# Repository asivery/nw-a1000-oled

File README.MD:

# A replacement display for the NW-A1000 Network Walkman

## How it works

Since the Sony NW-A1000 uses an obsolete SSD1328U1-based screen, to make it work with a generic SSD1327 screen I had to patch the firmware.

There's, of course, no new screens available with that exact pinout, so I designed a flex PCB which simply translates the pin layout to the one used by new OLEDs.

[Here](https://aliexpress.com/item/1005006480988390.html)'s the screen I used.

## How to patch?

1. Download the official Sony upgrade tool for the NW-A1000, and start it with the walkman unplugged.
2. Once you see this window, open task manager.

3. Open task manager, find `FWUpdater.exe`, right click, select `Open file location`. Then copy all the files to somewhere on your desktop.

4. Go to [my patching site](https://asivery.github.io/NW-A1000/), and provide it the `ver3.00/NW_A1000.UPG` file from that folder.
5. Download the new file, delete all files in `ver3.00` and replace them with the one from my site.
6. Run the patcher and flash the Walkman.

## Is the NW-A1200 / NW-A3000 supported?

I don't know - I haven't tested them with this method, but probably.

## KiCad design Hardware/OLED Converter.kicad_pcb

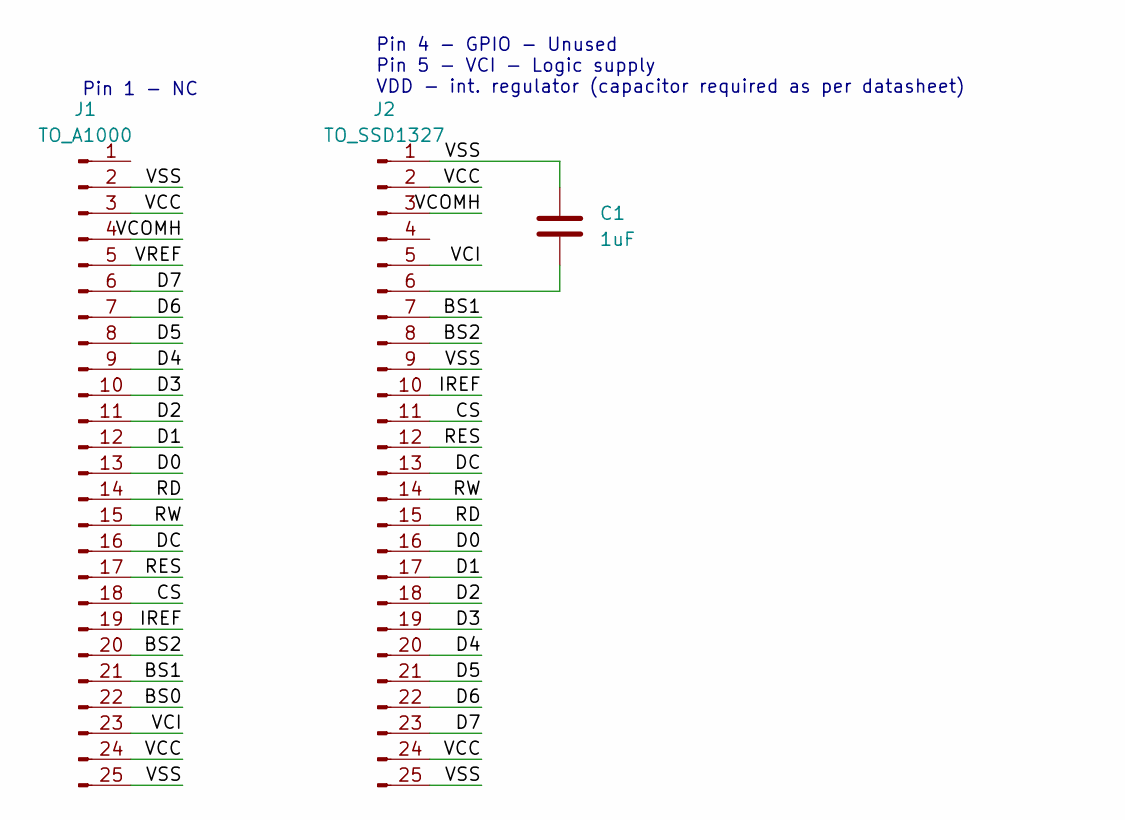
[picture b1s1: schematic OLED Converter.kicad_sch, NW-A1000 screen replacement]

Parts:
C1: 1uF; C_0402_1005Metric_Pad0.74x0.62mm_HandSolder
J1: TO_A1000; FFC25_0.3
J2: TO_SSD1327; SSD1327_ribbon

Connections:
/BS0: J1.22
/BS1: J1.21, J2.7
/BS2: J1.20, J2.8
/CS: J1.18, J2.11
/D0: J1.13, J2.16
/D1: J1.12, J2.17
/D2: J1.11, J2.18
/D3: J1.10, J2.19
/D4: J1.9, J2.20
/D5: J1.8, J2.21
/D6: J1.7, J2.22
/D7: J1.6, J2.23
/DC: J1.16, J2.13
/IREF: J1.19, J2.10
/RD: J1.14, J2.15
/RES: J1.17, J2.12
/RW: J1.15, J2.14
/VCC: J1.3, J1.24, J2.2, J2.24
/VCI: J1.23, J2.5
/VCOMH: J1.4, J2.3
/VREF: J1.5
/VSS: C1.1, J1.2, J1.25, J2.1, J2.9, J2.25
unnamed: C1.2, J2.6

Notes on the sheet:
Pin 4 - GPIO - Unused Pin 5 - VCI - Logic supply VDD - int. regulator (capacitor required as per datasheet)
Pin 1 - NC

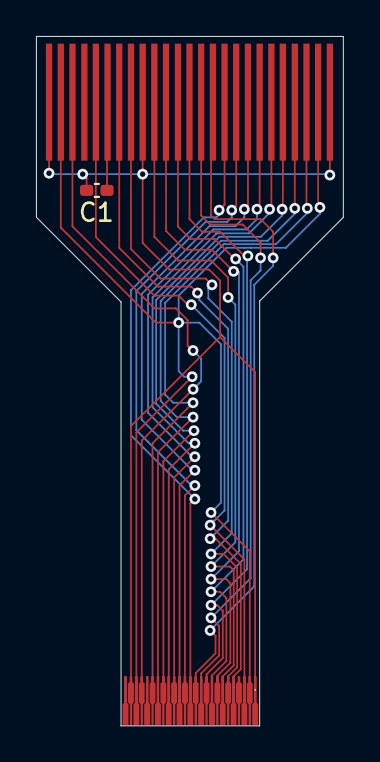
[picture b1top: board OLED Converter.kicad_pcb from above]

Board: 2 copper layers, 17.1 x 38.3 mm, 3 parts (0 on the bottom side), 21 nets.

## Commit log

2025-05-28 Add image
2025-05-28 Add link to screen
2025-05-29 Add production files
